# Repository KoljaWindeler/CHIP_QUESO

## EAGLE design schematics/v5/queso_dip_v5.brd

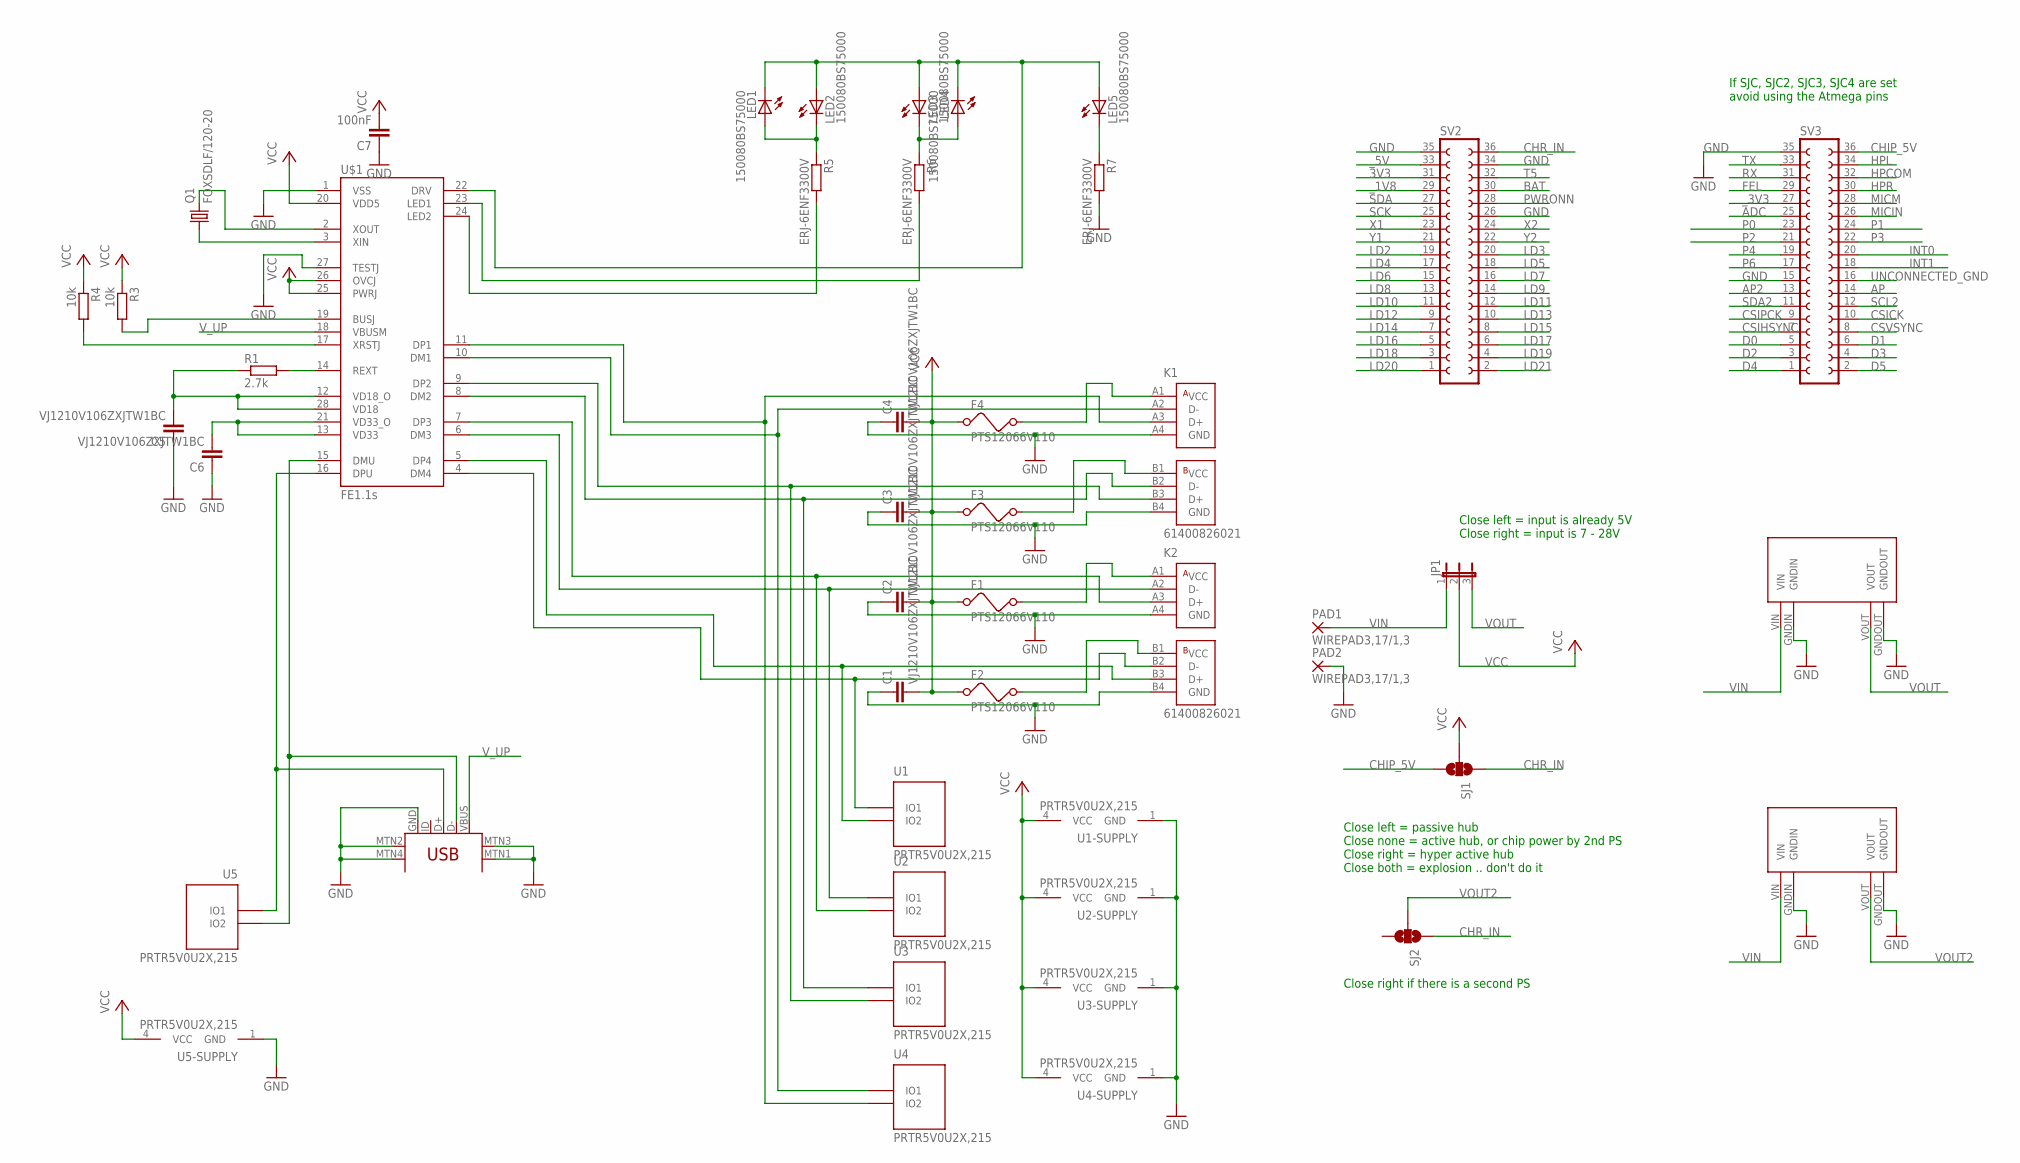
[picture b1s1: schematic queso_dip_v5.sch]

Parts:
C1, C2, C3, C4, C5, C6: VJ1210V106ZXJTW1BC; C1210
C7: 100nF; C0805
F1, F2, F3, F4: PTS12066V110; 1210
JP1: JP2E; JP2
K1, K2: 61400826021
LED1, LED2, LED3, LED4, LED5: 150080BS75000; CHIP-LED0805
PAD1, PAD2: WIREPAD3,17/1,3; 3,17/1,3
Q1: FOXSDLF/120-20; SM49
R1: 2.7k; R0805
R3, R4: 10k; R0805
R5, R6, R7: ERJ-6ENF3300V; R0805
SJ1, SJ2: SOLDERJUMPER_2WAYT; SJ_2
SV2, SV3: FE18-2
U1, U2, U3, U4, U5: PRTR5V0U2X,215; SOT-143B
U$1: FE1.1S; FE1.1S_SSOP-28
U$3, U$9: MP1584EN
U$8: 10118194-0001LF; USB-MINIB

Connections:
3V3: SV2.31
ADC: SV3.25
AP: SV3.14
AP2: SV3.13
BAT: SV2.30
CHIP_5V: SJ1.3, SV3.36
CHR_IN: SJ1.1, SJ2.1, SV2.36
CSICK: SV3.10
CSIHSYNC: SV3.7
CSIPCK: SV3.9
CSVSYNC: SV3.8
D0: SV3.5
D1: SV3.6
D2: SV3.3
D3: SV3.4
D4: SV3.1
D5: SV3.2
DM1: K1.A2 (D-), U4.2 (IO1), U$1.10 (DM1)
DM2: K1.B2 (D-), U3.2 (IO1), U$1.8 (DM2)
DM3: K2.A2 (D-), U2.2 (IO1), U$1.6 (DM3)
DM4: K2.B2 (D-), U1.2 (IO1), U$1.4 (DM4)
DMU: U5.3 (IO2), U$1.15 (DMU), U$8.D-
DP1: K1.A3 (D+), U4.3 (IO2), U$1.11 (DP1)
DP2: K1.B3 (D+), U3.3 (IO2), U$1.9 (DP2)
DP3: K2.A3 (D+), U2.3 (IO2), U$1.7 (DP3)
DP4: K2.B3 (D+), U1.3 (IO2), U$1.5 (DP4)
DPU: U5.2 (IO1), U$1.16 (DPU), U$8.D+
FEL: SV3.29
GND: C1.1, C2.1, C3.1, C4.1, C5.1, C6.1, C7.1, K1.A4 (GND), K1.B4 (GND), K2.A4 (GND), K2.B4 (GND), PAD2.1, R7.2, SV2.26, SV2.34, SV2.35, SV3.15, SV3.35, U1.1 (GND), U2.1 (GND), U3.1 (GND), U4.1 (GND), U5.1 (GND), U$1.1 (VSS), U$1.27 (TESTJ), U$3.GNDIN, U$3.GNDOUT, U$8.GND, U$8.MTN1 (MTN2), U$8.MTN2 (MTN3), U$8.MTN3 (MTN1), U$8.MTN4, U$9.GNDIN, U$9.GNDOUT
HPCOM: SV3.32
HPL: SV3.34
HPR: SV3.30
INT0: SV3.20
INT1: SV3.18
LD2: SV2.19
LD3: SV2.20
LD4: SV2.17
LD5: SV2.18
LD6: SV2.15
LD7: SV2.16
LD8: SV2.13
LD9: SV2.14
LD10: SV2.11
LD11: SV2.12
LD12: SV2.9
LD13: SV2.10
LD14: SV2.7
LD15: SV2.8
LD16: SV2.5
LD17: SV2.6
LD18: SV2.3
LD19: SV2.4
LD20: SV2.1
LD21: SV2.2
MICIN: SV3.26
MICM: SV3.28
unnamed: F2.2, K2.B1 (VCC)
unnamed: F1.2, K2.A1 (VCC)
unnamed: F3.2, K1.B1 (VCC)
unnamed: F4.2, K1.A1 (VCC)
unnamed: R5.2, U$1.24 (LED2)
unnamed: R6.2, U$1.23 (LED1)
unnamed: C6.2, U$1.13 (VD33), U$1.21 (VD33_O)
unnamed: C5.2, R1.1, U$1.12 (VD18_O), U$1.28 (VD18)
unnamed: R1.2, U$1.14 (REXT)
unnamed: R4.2, U$1.17 (XRSTJ)
unnamed: R3.2, U$1.19 (BUSJ)
unnamed: Q1.2, U$1.2 (XOUT)
unnamed: Q1.1, U$1.3 (XIN)
unnamed: LED5.C, R7.1
unnamed: LED3.C, LED4.A, R6.1
unnamed: LED1.A, LED2.C, R5.1
unnamed: LED1.C, LED2.A, LED3.A, LED4.C, LED5.A, U$1.22 (DRV)
P0: SV3.23
P1: SV3.24
P2: SV3.21
P3: SV3.22
P4: SV3.19
P6: SV3.17
PWRONN: SV2.28
RX: SV3.31
SCK: SV2.25
SCL2: SV3.12
SDA: SV2.27
SDA2: SV3.11
T5: SV2.32
TX: SV3.33
UNCONNECTED_GND: SV3.16
VCC: C1.2, C2.2, C3.2, C4.2, C7.2, F1.1, F2.1, F3.1, F4.1, JP1.2, R3.1, R4.1, SJ1.2, U1.4 (VCC), U2.4 (VCC), U3.4 (VCC), U4.4 (VCC), U5.4 (VCC), U$1.20 (VDD5), U$1.25 (PWRJ), U$1.26 (OVCJ)
VIN: JP1.1, PAD1.1, U$3.VIN, U$9.VIN
VOUT: JP1.3, U$9.VOUT
VOUT2: SJ2.2, U$3.VOUT
V_UP: U$1.18 (VBUSM), U$8.VBUS
X1: SV2.23
X2: SV2.24
Y1: SV2.21
Y2: SV2.22
_1V8: SV2.29
_3V3: SV3.27
_5V: SV2.33

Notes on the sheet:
If SJC, SJC2, SJC3, SJC4 are set avoid using the Atmega pins
Close left = passive hub Close none = active hub, or chip power by 2nd PS Close right = hyper active hub Close both = explosion .. don't do it
Close left = input is already 5V Close right = input is 7 - 28V
Close right if there is a second PS

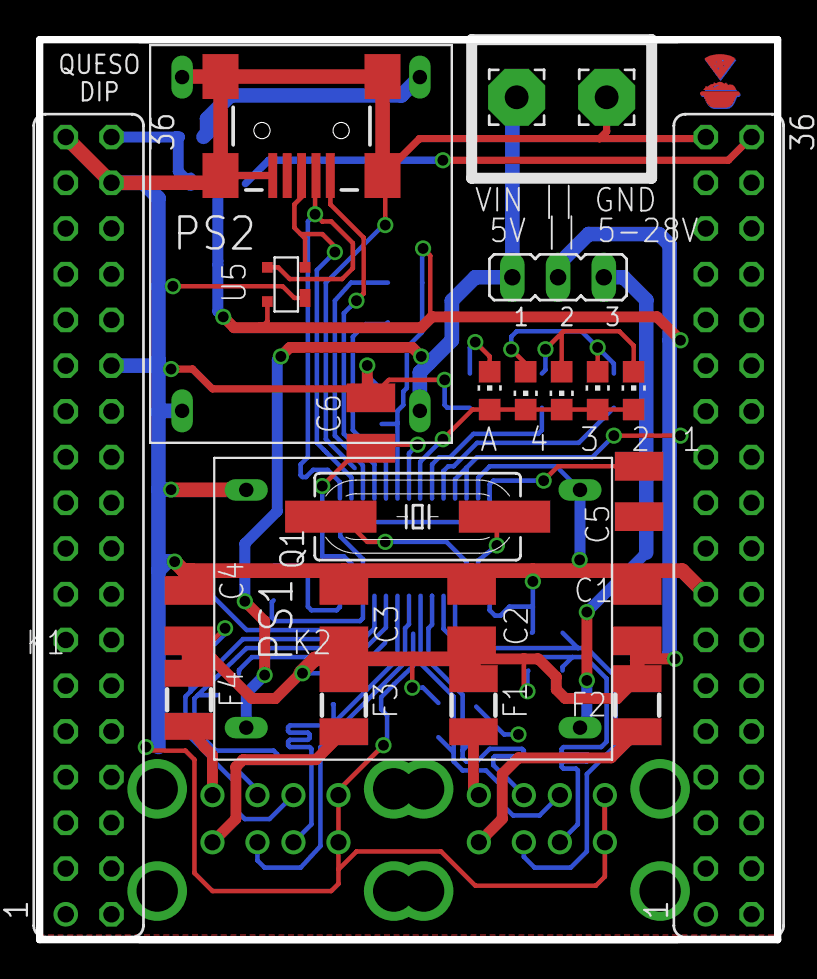
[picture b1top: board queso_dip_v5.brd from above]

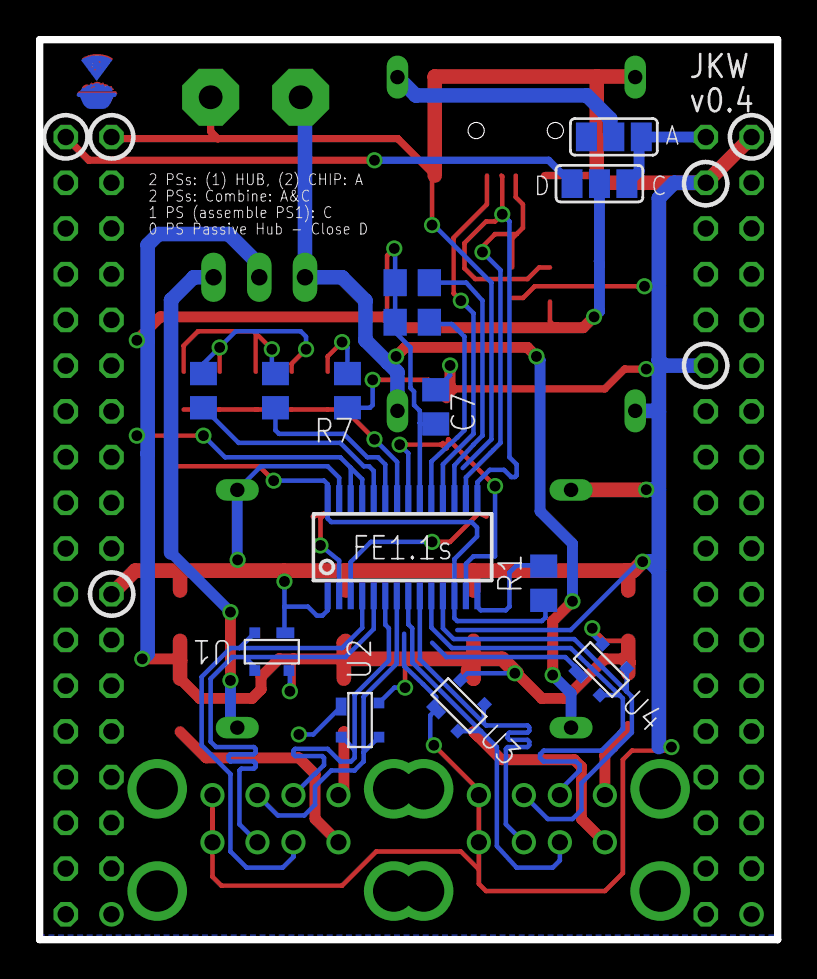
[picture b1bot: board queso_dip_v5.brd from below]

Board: 2 copper layers, 41.0 x 50.0 mm, 43 parts (15 on the bottom side), 35 nets.

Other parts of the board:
U$2, U$5: LOGO

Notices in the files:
parts and their libraries:
SparkFun-Connectors: Licensing: Creative Commons ShareAlike 4.0 International - https://creativecommons.org/licenses/by-sa/4.0
m-pad-2.1: License : GNU General Public License version 2 (see bottom)
Wuerth_Elektronik_eiCan_Communication_Co: Copyright: Würth Elektronik
